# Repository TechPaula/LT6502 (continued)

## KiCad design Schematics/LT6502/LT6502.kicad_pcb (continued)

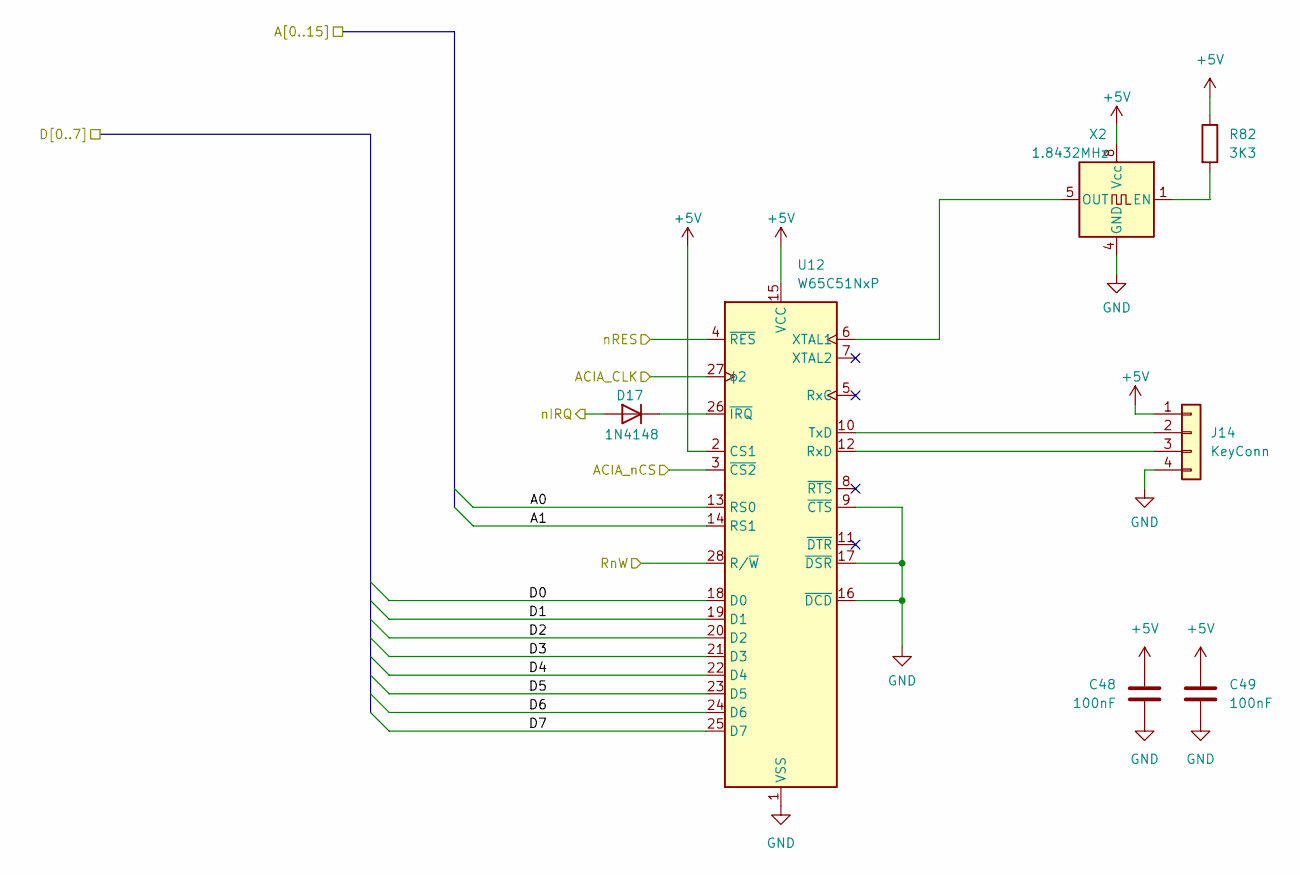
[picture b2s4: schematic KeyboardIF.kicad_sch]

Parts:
C48, C49: 100nF; C_0603_1608Metric; LCSC C113803
D17: 1N4148; D_DO-35_SOD27_P7.62mm_Horizontal; LCSC DNF
J14: KeyConn; PinHeader_1x04_P2.54mm_Horizontal; LCSC DNF
R82: 3K3; R_0402_1005Metric; LCSC C25890
U12: W65C51NxP; DIP-28_W15.24mm; LCSC DNF
X2: 1.8432MHz; Oscillator_DIP-8; Mouser Part Number 774-MXO45HST-3C-1.8; LCSC DNF

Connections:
+5V: C48.1, C49.1, J14.1, R82.1, U12.2 (CS1), U12.15 (VCC), X2.8 (Vcc); also elsewhere on the board
/A0: U12.13 (RS0); also elsewhere on the board
/A1: U12.14 (RS1); also elsewhere on the board
/D0: U12.18 (D0); also elsewhere on the board
/D1: U12.19 (D1); also elsewhere on the board
/D2: U12.20 (D2); also elsewhere on the board
/D3: U12.21 (D3); also elsewhere on the board
/D4: U12.22 (D4); also elsewhere on the board
/D5: U12.23 (D5); also elsewhere on the board
/D6: U12.24 (D6); also elsewhere on the board
/D7: U12.25 (D7); also elsewhere on the board
ACIA_nCS: U12.3 (~CS2); also elsewhere on the board
CLK: U12.27 (ϕ2); also elsewhere on the board
GND: C48.2, C49.2, J14.4, U12.1 (VSS), U12.9 (~CTS), U12.16 (~DCD), U12.17 (~DSR), X2.4 (GND); also elsewhere on the board
unnamed: D17.1 (K), U12.26 (~IRQ)
unnamed: J14.2, U12.10 (TxD)
unnamed: J14.3, U12.12 (RxD)
unnamed: U12.6 (XTAL1), X2.5 (OUT)
unnamed: R82.2, X2.1 (EN)
RnW: U12.28 (R/~W); also elsewhere on the board
nIRQ: D17.2 (A); also elsewhere on the board
nRES: U12.4 (~RES); also elsewhere on the board

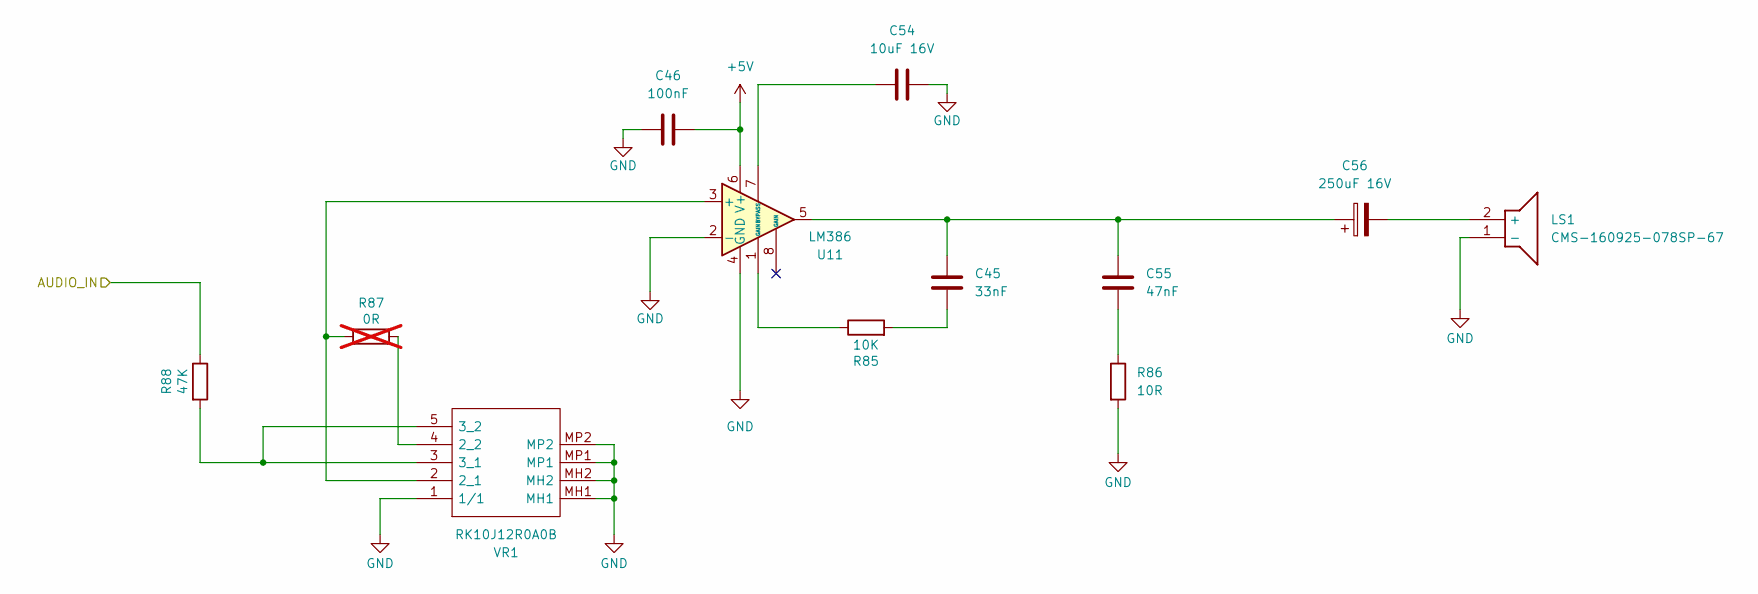
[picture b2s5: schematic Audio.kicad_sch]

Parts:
C45: 33nF; C_0603_1608Metric; LCSC C21117
C46: 100nF; C_0603_1608Metric; LCSC C113803
C54: 10uF 16V; C_0805_2012Metric; LCSC C15850
C55: 47nF; C_0603_1608Metric; LCSC C1622
C56: 250uF 16V; CP_Elec_10x12.5; Mouser Part Number 667-EEV-FK1V681Q
LS1: CMS-160925-078SP-67; CMS160925078SP67; Mouser Part Number 490-CMS160925078SP67
R85: 10K; R_0402_1005Metric; LCSC C25744
R86: 10R; R_0805_2012Metric; LCSC C844598
R87: 0R; R_0402_1005Metric; LCSC DNF; not fitted
R88: 47K; R_0402_1005Metric; LCSC DNF
U11: LM386; DIP-8_W7.62mm; Mouser Part Number 926-LM386N-3/NOPB
VR1: RK10J12R0A0B; Mouser Part Number 688-RK10J12R0A0B

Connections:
+5V: C46.2, U11.6 (V+); also elsewhere on the board
AUDIO: R88.1; also elsewhere on the board
GND: C46.1, C54.1, LS1.1 (-), R86.2, U11.2 (-), U11.4 (GND), VR1.1 (1/1), VR1.MH1, VR1.MH2, VR1.MP1, VR1.MP2; also elsewhere on the board
unnamed: C45.1, C55.1, C56.1, U11.5
unnamed: C45.2, R85.2
unnamed: C55.2, R86.1
unnamed: C56.2, LS1.2 (+)
unnamed: R85.1, U11.1 (GAIN)
unnamed: R87.2, U11.3 (+), VR1.2 (2_1)
unnamed: C54.2, U11.7 (BYPASS)
unnamed: R87.1, VR1.4 (2_2)
unnamed: R88.2, VR1.3 (3_1), VR1.5 (3_2)

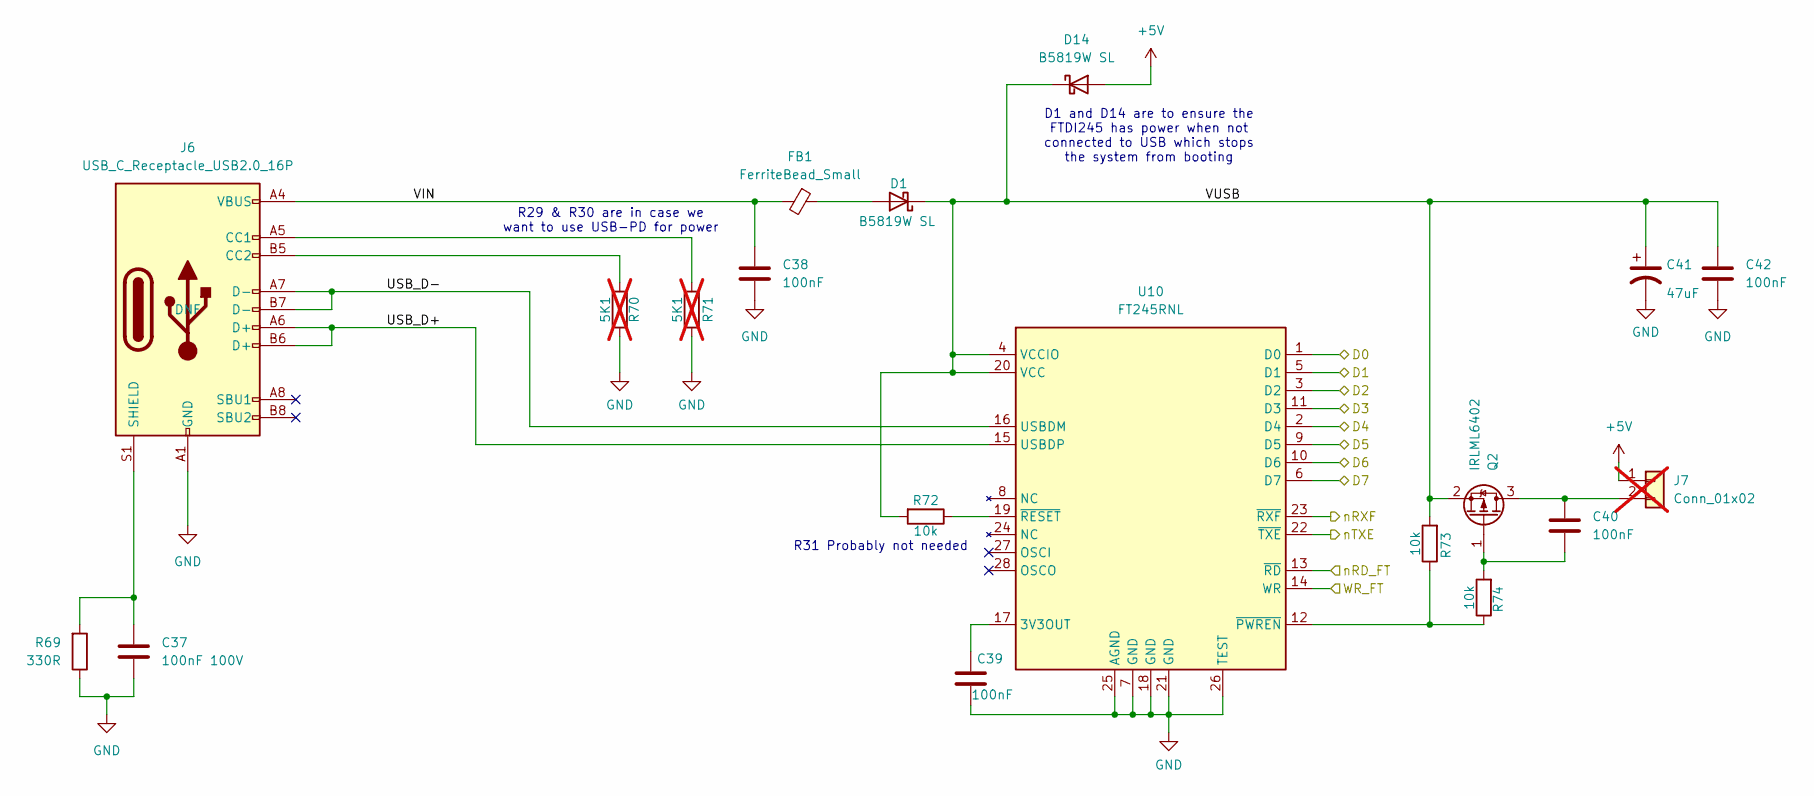
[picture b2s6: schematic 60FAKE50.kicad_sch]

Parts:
C37: 100nF 100V; C_0603_1608Metric; LCSC C113803
C38, C42: 100nF; C_0805_2012Metric; LCSC C49678
C39, C40: 100nF; C_0603_1608Metric; LCSC C113803
C41: 47uF; C_1206_3216Metric; LCSC C22367835
D1, D14: B5819W SL; D_SOD-123; LCSC C8598
FB1: FerriteBead_Small; L_0805_2012Metric_Pad1.05x1.20mm_HandSolder; LCSC DNF
J6: USB_C_Receptacle_USB2.0_16P; USB_C_Receptacle_HCTL_HC-TYPE-C-16P-01A; LCSC DNF
J7: Conn_01x02; PinHeader_1x02_P2.54mm_Horizontal; LCSC DNF; not fitted
Q2: IRLML6402; SOT-23; Mouser Part Number 942-IRLML6402TRPBF; LCSC C2593
R69: 330R; R_0402_1005Metric; LCSC C25104
R70, R71: 5K1; R_0402_1005Metric; LCSC DNF; not fitted
R72, R73, R74: 10k; R_0402_1005Metric; LCSC C25744
U10: FT245RNL; SSOP-28_5.3x10.2mm_P0.65mm; Mouser Part Number 895-FT245RNL-REEL; LCSC DNF

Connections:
+5V: D14.2 (A), J7.1; also elsewhere on the board
/60FAKE50/USB_D+: J6.A6 (D+), J6.B6 (D+), U10.15 (USBDP)
/60FAKE50/USB_D-: J6.A7 (D-), J6.B7 (D-), U10.16 (USBDM)
/60FAKE50/VIN: C38.1, FB1.2, J6.A4 (VBUS), J6.A9 (VBUS), J6.B4 (VBUS), J6.B9 (VBUS)
/60FAKE50/VUSB: C41.1, C42.1, D1.1 (K), D14.1 (K), Q2.2 (S), R72.2, R73.2, U10.4 (VCCIO), U10.20 (VCC)
/D0: U10.1 (D0); also elsewhere on the board
/D1: U10.5 (D1); also elsewhere on the board
/D2: U10.3 (D2); also elsewhere on the board
/D3: U10.11 (D3); also elsewhere on the board
/D4: U10.2 (D4); also elsewhere on the board
/D5: U10.9 (D5); also elsewhere on the board
/D6: U10.10 (D6); also elsewhere on the board
/D7: U10.6 (D7); also elsewhere on the board
GND: C37.2, C38.2, C39.2, C41.2, C42.2, J6.A1 (GND), J6.A12 (GND), J6.B1 (GND), J6.B12 (GND), R69.1, R70.1, R71.1, U10.7 (GND), U10.18 (GND), U10.21 (GND), U10.25 (AGND), U10.26 (TEST); also elsewhere on the board
unnamed: D1.2 (A), FB1.1
unnamed: J6.A5 (CC1), R71.2
unnamed: J6.B5 (CC2), R70.2
unnamed: C37.1, J6.S1 (SHIELD), R69.2
unnamed: C40.1, J7.2, Q2.3 (D)
unnamed: C40.2, Q2.1 (G), R74.2
unnamed: C39.1, U10.17 (3V3OUT)
unnamed: R73.1, R74.1, U10.12 (~PWREN)
unnamed: R72.1, U10.19 (~RESET)
WR_FT: U10.14 (WR); also elsewhere on the board
nRD_FT: U10.13 (~RD); also elsewhere on the board
nRXF: U10.23 (~RXF); also elsewhere on the board
nTXE: U10.22 (~TXE); also elsewhere on the board

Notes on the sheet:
D1 and D14 are to ensure the FTDI245 has power when not connected to USB which stops the system from booting
R31 Probably not needed
R29 & R30 are in case we want to use USB-PD for power

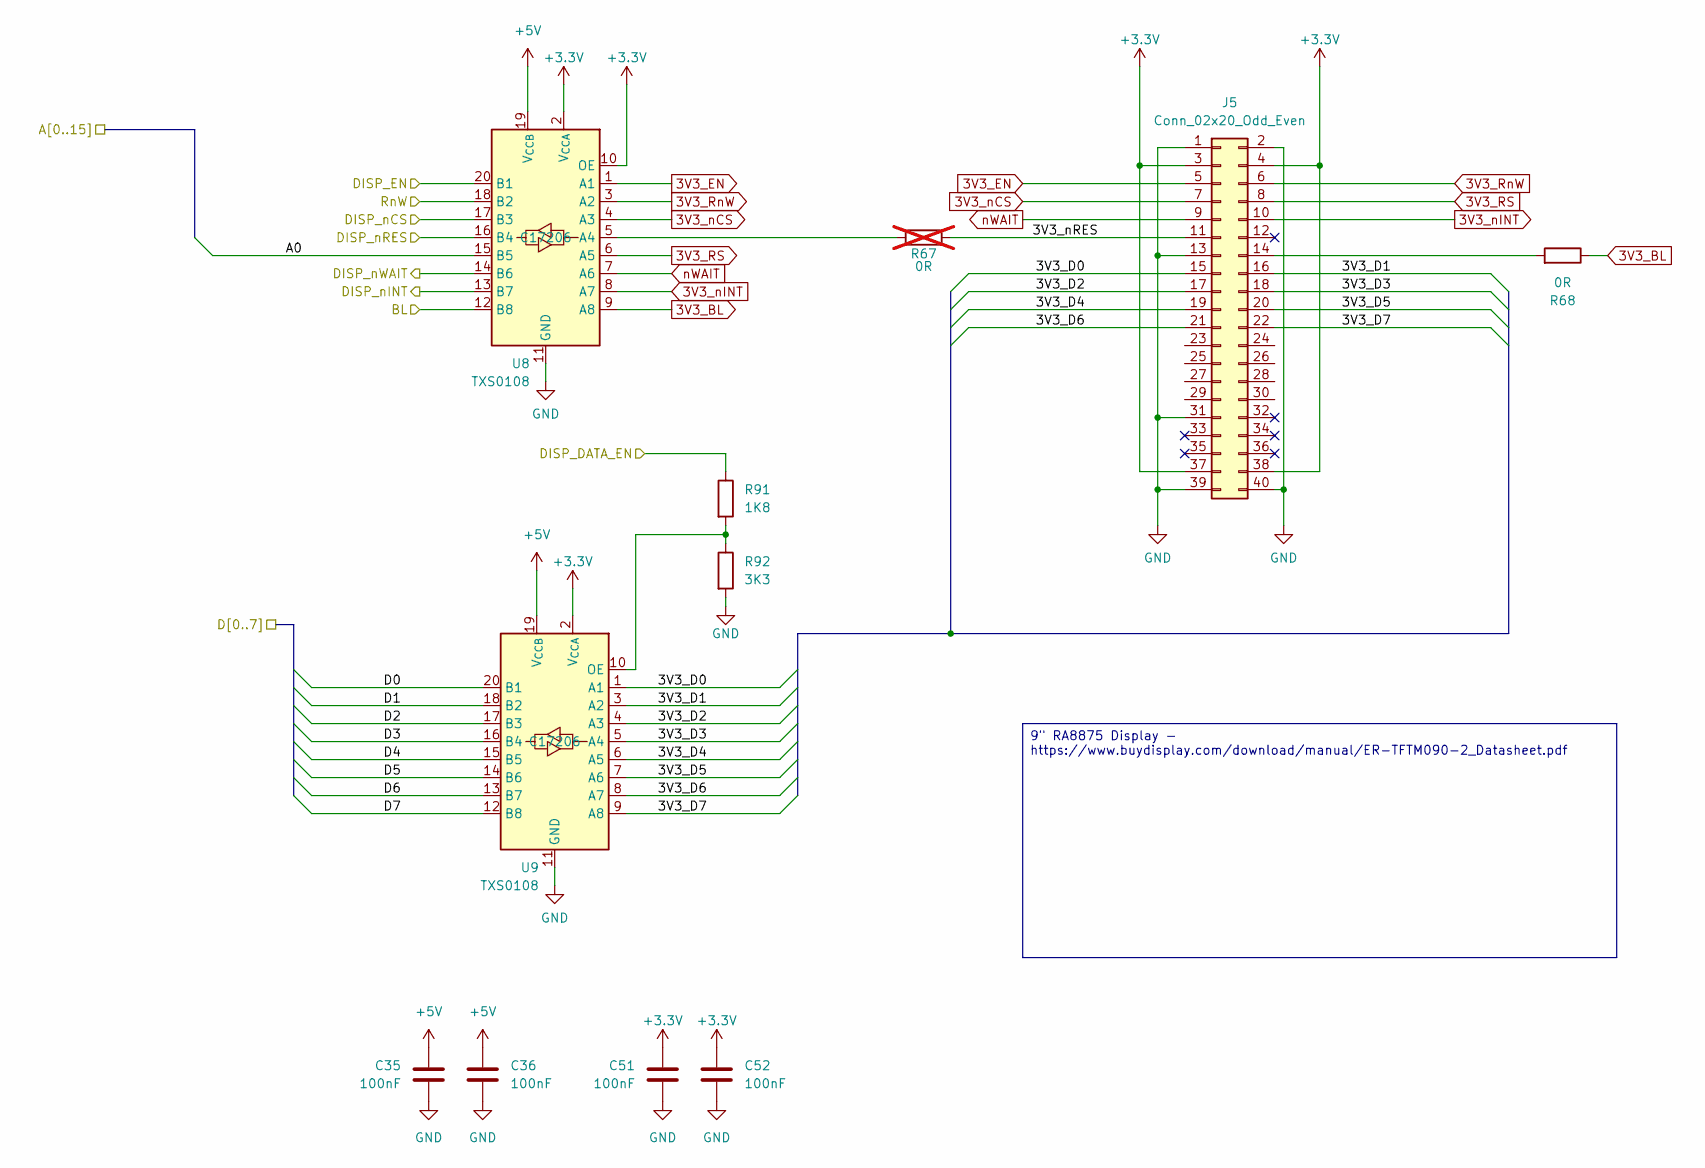
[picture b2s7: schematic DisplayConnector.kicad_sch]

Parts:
C35, C36, C51, C52: 100nF; C_0603_1608Metric; LCSC C113803
J5: Conn_02x20_Odd_Even; PinHeader_2x20_P2.54mm_Vertical; LCSC DNF
R67: 0R; R_0402_1005Metric; LCSC DNF; not fitted
R68: 0R; R_0402_1005Metric; LCSC DNF
R91: 1K8; R_0603_1608Metric; LCSC C25890
R92: 3K3; R_0603_1608Metric; LCSC C25890
U8, U9: TXS0108; TSSOP-20_4.4x6.5mm_P0.65mm; Mouser Part Number 595-TXB0108PWR; LCSC C17206

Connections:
3V3_BL: R68.1, U8.9 (A8)
3V3_EN: J5.5, U8.1 (A1)
3V3_RS: J5.8, U8.6 (A5)
3V3_RnW: J5.6, U8.3 (A2)
3V3_nCS: J5.7, U8.4 (A3)
3V3_nINT: J5.10, U8.8 (A7)
+3.3V: C51.1, C52.1, J5.3, J5.4, J5.37, J5.38, U8.2 (V_{CCA}), U8.10 (OE), U9.2 (V_{CCA}); also elsewhere on the board
+5V: C35.1, C36.1, U8.19 (V_{CCB}), U9.19 (V_{CCB}); also elsewhere on the board
/A0: U8.15 (B5); also elsewhere on the board
/D0: U9.20 (B1); also elsewhere on the board
/D1: U9.18 (B2); also elsewhere on the board
/D2: U9.17 (B3); also elsewhere on the board
/D3: U9.16 (B4); also elsewhere on the board
/D4: U9.15 (B5); also elsewhere on the board
/D5: U9.14 (B6); also elsewhere on the board
/D6: U9.13 (B7); also elsewhere on the board
/D7: U9.12 (B8); also elsewhere on the board
/Display Connector/3V3_D0: J5.15, U9.1 (A1)
/Display Connector/3V3_D1: J5.16, U9.3 (A2)
/Display Connector/3V3_D2: J5.17, U9.4 (A3)
/Display Connector/3V3_D3: J5.18, U9.5 (A4)
/Display Connector/3V3_D4: J5.19, U9.6 (A5)
/Display Connector/3V3_D5: J5.20, U9.7 (A6)
/Display Connector/3V3_D6: J5.21, U9.8 (A7)
/Display Connector/3V3_D7: J5.22, U9.9 (A8)
/Display Connector/3V3_nRES: J5.11, R67.2
/Display Connector/BL: U8.12 (B8); also elsewhere on the board
/Display Connector/DISP_DATA_EN: R91.1; also elsewhere on the board
/Display Connector/DISP_EN: U8.20 (B1); also elsewhere on the board
/Display Connector/DISP_nCS: U8.17 (B3); also elsewhere on the board
/Display Connector/DISP_nINT: U8.13 (B7); also elsewhere on the board
/Display Connector/DISP_nRES: U8.16 (B4); also elsewhere on the board
/Display Connector/DISP_nWAIT: U8.14 (B6); also elsewhere on the board
GND: C35.2, C36.2, C51.2, C52.2, J5.1, J5.2, J5.13, J5.31, J5.39, J5.40, R92.2, U8.11 (GND), U9.11 (GND); also elsewhere on the board
unnamed: J5.14, R68.2
unnamed: R67.1, U8.5 (A4)
unnamed: R91.2, R92.1, U9.10 (OE)
RnW: U8.18 (B2); also elsewhere on the board
nWAIT: J5.9, U8.7 (A6)

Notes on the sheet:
9" RA8875 Display - https://www.buydisplay.com/download/manual/ER-TFTM090-2_Datasheet.pdf

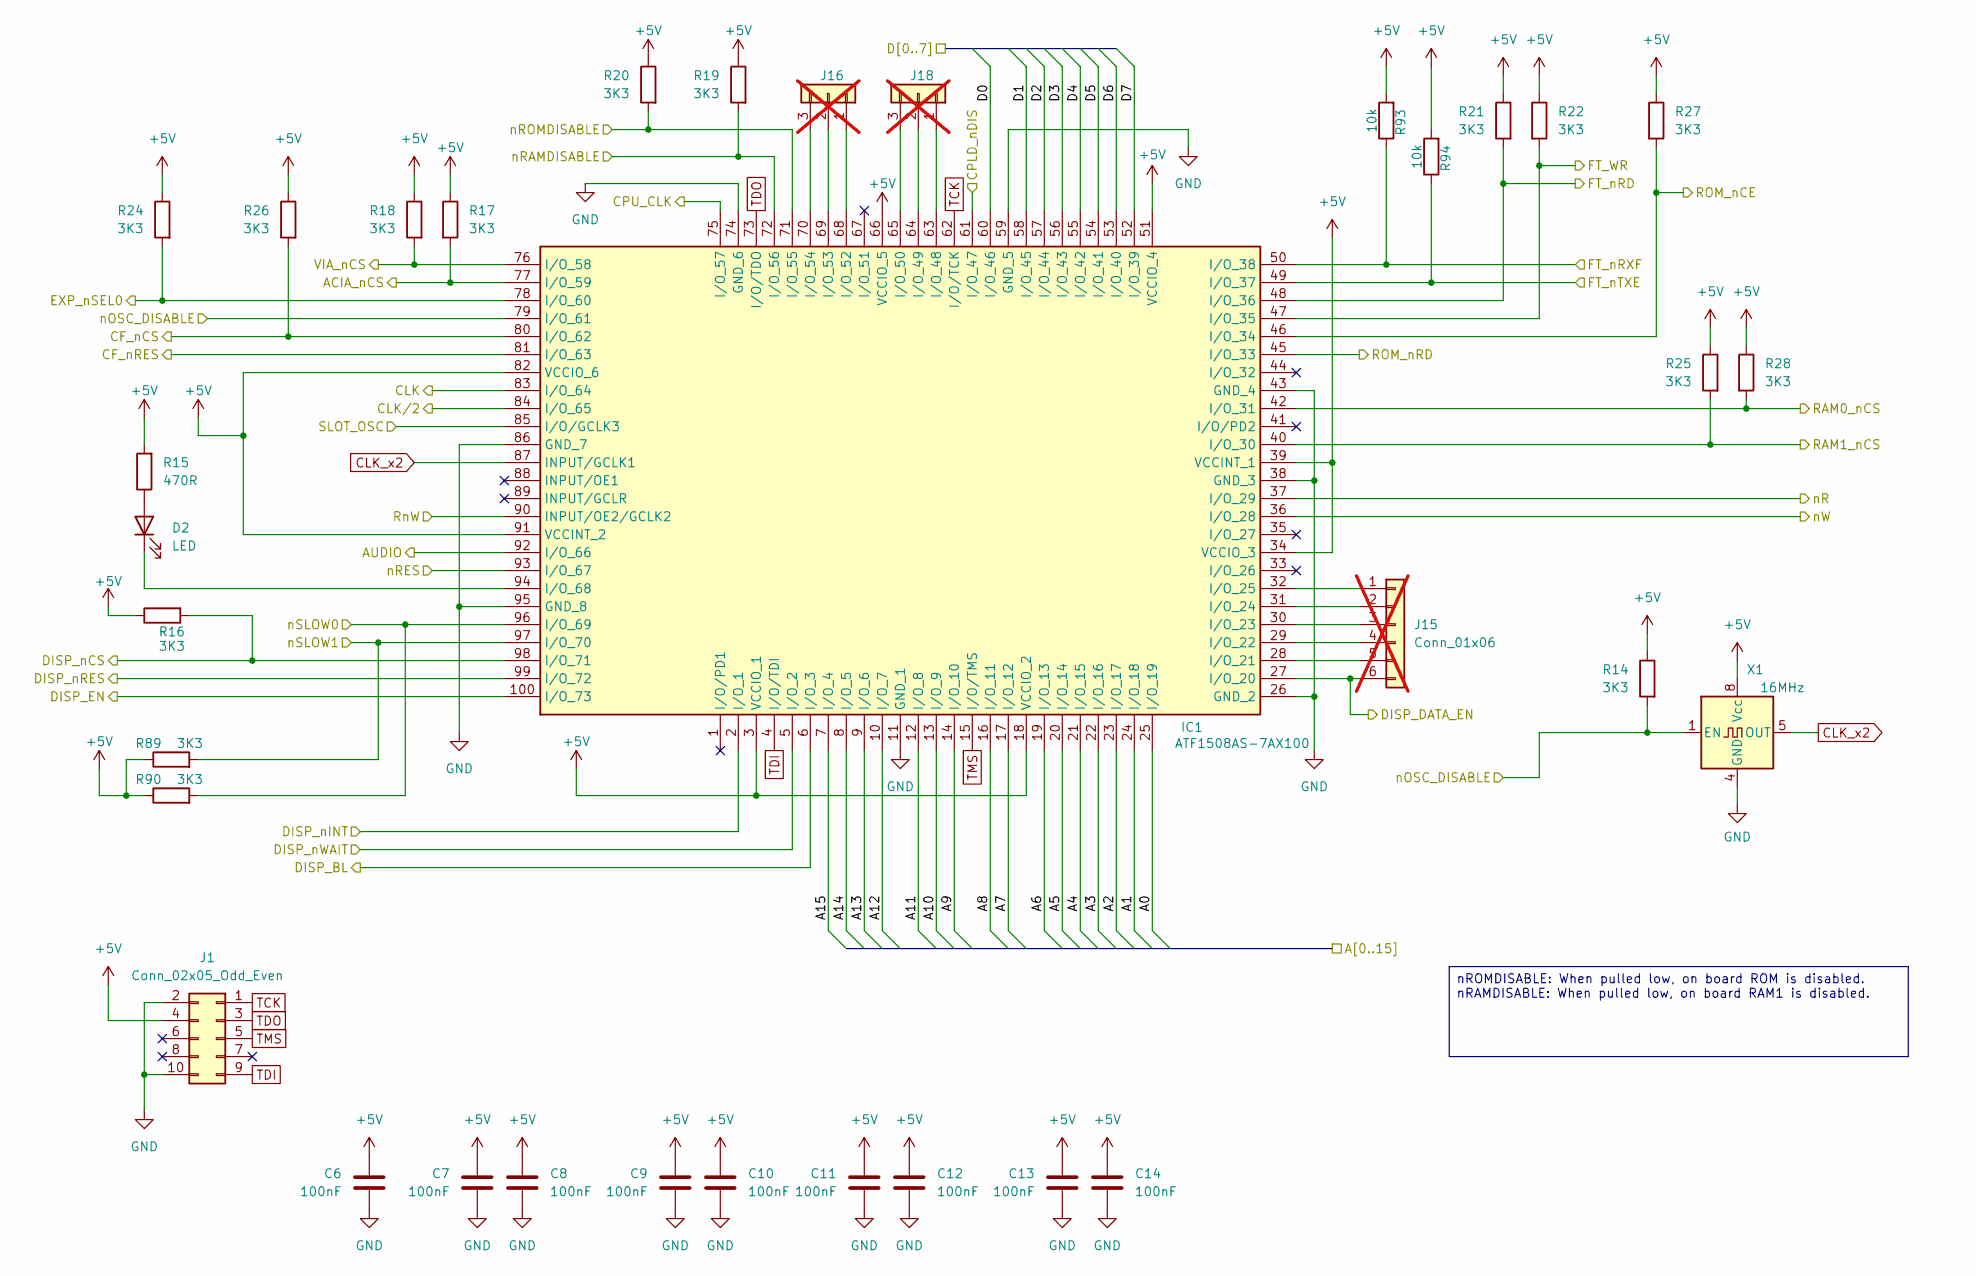
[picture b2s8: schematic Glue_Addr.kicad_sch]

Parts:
C6, C7, C8, C9, C11, C12, C13, C14: 100nF; C_0603_1608Metric; LCSC C113803
C10: 100nF; C_0402_1005Metric; LCSC C1581
D2: LED; LED_0603_1608Metric; LCSC DNF
IC1: ATF1508AS-7AX100; QFP50P1600X1600X120-100N; Mouser Part Number 556-AF1508AS7AX100
J1: Conn_02x05_Odd_Even; PinHeader_2x05_P2.54mm_Horizontal; LCSC DNF
J15: Conn_01x06; PinHeader_1x06_P1.00mm_Vertical_SMD_Pin1Left; LCSC DNF; not fitted
J16, J18: Conn_01x03; PinHeader_1x03_P1.00mm_Vertical_SMD_Pin1Left; LCSC DNF; not fitted
R14, R16, R17, R18, R19, R20, R21, R22, R24, R25, R26, R27, R28, R89, R90: 3K3; R_0402_1005Metric; LCSC C25890
R15: 470R; R_0402_1005Metric; LCSC C25117
R93, R94: 10k; R_0402_1005Metric; LCSC C25744
X1: 16MHz; Oscillator_DIP-8; Mouser Part Number 520-2100AX-283.2; LCSC DNF

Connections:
+5V: C6.1, C7.1, C8.1, C9.1, C10.1, C11.1, C12.1, C13.1, C14.1, IC1.3 (VCCIO_1), IC1.18 (VCCIO_2), IC1.34 (VCCIO_3), IC1.39 (VCCINT_1), IC1.51 (VCCIO_4), IC1.66 (VCCIO_5), IC1.82 (VCCIO_6), IC1.91 (VCCINT_2), J1.4, R14.1, R15.2, R16.1, R17.1, R18.1, R19.1, R20.1, R21.1, R22.1, R24.1, R25.1, R26.1, R27.1, R28.1, R89.1, R90.1, R93.2, R94.2, X1.8 (Vcc); also elsewhere on the board
/A0: IC1.25 (I/O_19); also elsewhere on the board
/A1: IC1.24 (I/O_18); also elsewhere on the board
/A2: IC1.23 (I/O_17); also elsewhere on the board
/A3: IC1.22 (I/O_16); also elsewhere on the board
/A4: IC1.21 (I/O_15); also elsewhere on the board
/A5: IC1.20 (I/O_14); also elsewhere on the board
/A6: IC1.19 (I/O_13); also elsewhere on the board
/A7: IC1.17 (I/O_12); also elsewhere on the board
/A8: IC1.16 (I/O_11); also elsewhere on the board
/A9: IC1.14 (I/O_10); also elsewhere on the board
/A10: IC1.13 (I/O_9); also elsewhere on the board
/A11: IC1.12 (I/O_8); also elsewhere on the board
/A12: IC1.10 (I/O_7); also elsewhere on the board
/A13: IC1.9 (I/O_6); also elsewhere on the board
/A14: IC1.8 (I/O_5); also elsewhere on the board
/A15: IC1.7 (I/O_4); also elsewhere on the board
/D0: IC1.60 (I/O_46); also elsewhere on the board
/D1: IC1.58 (I/O_45); also elsewhere on the board
/D2: IC1.57 (I/O_44); also elsewhere on the board
/D3: IC1.56 (I/O_43); also elsewhere on the board
/D4: IC1.55 (I/O_42); also elsewhere on the board
/D5: IC1.54 (I/O_41); also elsewhere on the board
/D6: IC1.53 (I/O_40); also elsewhere on the board
/D7: IC1.52 (I/O_39); also elsewhere on the board
/Display Connector/BL: IC1.6 (I/O_3); also elsewhere on the board
/Display Connector/DISP_DATA_EN: IC1.27 (I/O_20), J15.6; also elsewhere on the board
/Display Connector/DISP_EN: IC1.100 (I/O_73); also elsewhere on the board
/Display Connector/DISP_nCS: IC1.98 (I/O_71), R16.2; also elsewhere on the board
/Display Connector/DISP_nINT: IC1.2 (I/O_1); also elsewhere on the board
/Display Connector/DISP_nRES: IC1.99 (I/O_72); also elsewhere on the board
/Display Connector/DISP_nWAIT: IC1.5 (I/O_2); also elsewhere on the board
/ExpansionSlot0/CPLD_nDIS: IC1.61 (I/O_47); also elsewhere on the board
ACIA_nCS: IC1.77 (I/O_59), R17.2; also elsewhere on the board
AUDIO: IC1.92 (I/O_66); also elsewhere on the board
CFnRES: IC1.80 (I/O_62), R26.2; also elsewhere on the board
CLK: IC1.83 (I/O_64); also elsewhere on the board
CLK_x2: IC1.87 (INPUT/GCLK1), X1.5 (OUT)
CLK/2: IC1.84 (I/O_65); also elsewhere on the board
CPU_CLK: IC1.75 (I/O_57); also elsewhere on the board
EXP_nSEL0: IC1.78 (I/O_60), R24.2; also elsewhere on the board
GND: C6.2, C7.2, C8.2, C9.2, C10.2, C11.2, C12.2, C13.2, C14.2, IC1.11 (GND_1), IC1.26 (GND_2), IC1.38 (GND_3), IC1.43 (GND_4), IC1.59 (GND_5), IC1.74 (GND_6), IC1.86 (GND_7), IC1.95 (GND_8), J1.2, J1.10, X1.4 (GND); also elsewhere on the board
unnamed: D2.2 (A), R15.1
unnamed: D2.1 (K), IC1.94 (I/O_68)
unnamed: IC1.28 (I/O_21), J15.5
unnamed: IC1.29 (I/O_22), J15.4
unnamed: IC1.30 (I/O_23), J15.3
unnamed: IC1.31 (I/O_24), J15.2
unnamed: IC1.32 (I/O_25), J15.1
unnamed: IC1.63 (I/O_48), J18.1
unnamed: IC1.64 (I/O_49), J18.2
unnamed: IC1.65 (I/O_50), J18.3
unnamed: IC1.68 (I/O_52), J16.1
unnamed: IC1.69 (I/O_53), J16.2
unnamed: IC1.70 (I/O_54), J16.3
ROM_nCE: IC1.46 (I/O_34), R27.2; also elsewhere on the board
ROM_nR: IC1.45 (I/O_33); also elsewhere on the board
RnW: IC1.90 (INPUT/OE2/GCLK2); also elsewhere on the board
SLOT_OSC: IC1.85 (I/O/GCLK3); also elsewhere on the board
TCK: IC1.62 (I/O/TCK), J1.1
TDI: IC1.4 (I/O/TDI), J1.9
TDO: IC1.73 (I/O/TDO), J1.3
TMS: IC1.15 (I/O/TMS), J1.5
VIA_nCS: IC1.76 (I/O_58), R18.2; also elsewhere on the board
WR_FT: IC1.47 (I/O_35), R22.2; also elsewhere on the board
nCF_CS0: IC1.81 (I/O_63); also elsewhere on the board
nOSC_DISABLE: IC1.79 (I/O_61), R14.2, X1.1 (EN); also elsewhere on the board
nR: IC1.37 (I/O_29); also elsewhere on the board
nRAM0_CS: IC1.42 (I/O_31), R28.2; also elsewhere on the board
nRAM1_CS: IC1.40 (I/O_30), R25.2; also elsewhere on the board
nRAMDISABLE: IC1.72 (I/O_56), R19.2; also elsewhere on the board
nRD_FT: IC1.48 (I/O_36), R21.2; also elsewhere on the board
nRES: IC1.93 (I/O_67); also elsewhere on the board
nROMDISABLE: IC1.71 (I/O_55), R20.2; also elsewhere on the board
nRXF: IC1.49 (I/O_37), R94.1; also elsewhere on the board
nSLOW0: IC1.96 (I/O_69), R90.2; also elsewhere on the board
nSLOW1: IC1.97 (I/O_70), R89.2; also elsewhere on the board
nTXE: IC1.50 (I/O_38), R93.1; also elsewhere on the board
nW: IC1.36 (I/O_28); also elsewhere on the board

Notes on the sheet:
nROMDISABLE: When pulled low, on board ROM is disabled. nRAMDISABLE: When pulled low, on board RAM1 is disabled.

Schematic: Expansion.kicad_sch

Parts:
C43: 100nF; C_0603_1608Metric; LCSC C113803
C44: 22uF 25V; C_0805_2012Metric; LCSC C45783
D12, D13, D19, D21: 1N4148; D_DO-35_SOD27_P7.62mm_Horizontal; LCSC DNF
J9: DIN41612_02x32_AC; DIN41612_R_2x32_Female_Horizontal_THT; Mouser Part Number 649-864648813H55V1LF
R23: 3K3; R_0402_1005Metric; LCSC C25890

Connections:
+5V: C43.1, C44.1, J9.a2, J9.a31, J9.c2, J9.c31, R23.1; also elsewhere on the board
/A0: J9.c18; also elsewhere on the board
/A1: J9.a18; also elsewhere on the board
/A2: J9.c17; also elsewhere on the board
/A3: J9.a17; also elsewhere on the board
/A4: J9.c16; also elsewhere on the board
/A5: J9.a16; also elsewhere on the board
/A6: J9.c15; also elsewhere on the board
/A7: J9.a15; also elsewhere on the board
/A8: J9.c14; also elsewhere on the board
/A9: J9.a14; also elsewhere on the board
/A10: J9.c13; also elsewhere on the board
/A11: J9.a13; also elsewhere on the board
/A12: J9.c12; also elsewhere on the board
/A13: J9.a12; also elsewhere on the board
/A14: J9.c11; also elsewhere on the board
/A15: J9.a11; also elsewhere on the board
/D0: J9.c20; also elsewhere on the board
/D1: J9.a20; also elsewhere on the board
/D2: J9.c21; also elsewhere on the board
/D3: J9.a21; also elsewhere on the board
/D4: J9.c22; also elsewhere on the board
/D5: J9.a22; also elsewhere on the board
/D6: J9.c23; also elsewhere on the board
/D7: J9.a23; also elsewhere on the board
/ExpansionSlot0/CPLD_nDIS: J9.a28, R23.2; also elsewhere on the board
BE: J9.a25; also elsewhere on the board
CLK: J9.c8; also elsewhere on the board
CLK/2: J9.c9; also elsewhere on the board
CPU_CLK: J9.c7; also elsewhere on the board
EXP_nSEL0: J9.c30; also elsewhere on the board
GND: C43.2, C44.2, J9.a1, J9.a6, J9.a10, J9.a19, J9.a32, J9.c1, J9.c6, J9.c10, J9.c19, J9.c32; also elsewhere on the board
unnamed: D12.1 (K), J9.a29
unnamed: D13.1 (K), J9.a30
unnamed: D19.1 (K), J9.c28
unnamed: D21.1 (K), J9.c29
PHI1O: J9.a7; also elsewhere on the board
PHI2O: J9.a8; also elsewhere on the board
RDY: J9.a24; also elsewhere on the board
RnW: J9.c4; also elsewhere on the board
SLOT_OSC: J9.a9; also elsewhere on the board
SYNQ: J9.c25; also elsewhere on the board
nIRQ: J9.a27; also elsewhere on the board
nML: J9.c26; also elsewhere on the board
nNMI: J9.c27; also elsewhere on the board
nOSC_DISABLE: J9.a5; also elsewhere on the board
nRAMDISABLE: D12.2 (A); also elsewhere on the board
nRES: J9.c5; also elsewhere on the board
nROMDISABLE: D13.2 (A); also elsewhere on the board
nSLOW0: D19.2 (A); also elsewhere on the board
nSLOW1: D21.2 (A); also elsewhere on the board
nSO: J9.a26; also elsewhere on the board
nVP: J9.c24; also elsewhere on the board

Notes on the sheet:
I should have routed CLK/2 to the VIA/ACIA instead of the 16MHz Clock So I've swapped them in the CPLD.
As I'm unsure what I will do with these ports in the future I've added every CPU pin and a bunch of others that might be useful. nROMDISABLE: When pulled low, on board ROM is disabled. nRAMDISABLE: When pulled low, on board RAM1 is disabled. CPU_CLK could be stretched CLK is unstretched main clock 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

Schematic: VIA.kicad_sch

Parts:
C47: 100nF; C_0603_1608Metric; LCSC C113803
D16: 1N4148; D_DO-35_SOD27_P7.62mm_Horizontal; LCSC DNF
IC3: W65C22S6TQG-14; QFP80P1320X1320X270-44N; Mouser Part Number 955-W65C22S6TQG-14
J11: Conn_02x04_Odd_Even; PinSocket_2x04_P2.54mm_Horizontal; LCSC DNF
J12, J13: Conn_02x06_Odd_Even; PinSocket_2x06_P2.54mm_Horizontal; LCSC DNF

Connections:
+5V: C47.1, IC3.15 (VDD), IC3.20 (CS1), J11.1, J11.2, J12.1, J12.2, J13.1, J13.2; also elsewhere on the board
/A0: IC3.36 (RS0); also elsewhere on the board
/A1: IC3.35 (RS1); also elsewhere on the board
/A2: IC3.34 (RS2); also elsewhere on the board
/A3: IC3.33 (RS3); also elsewhere on the board
/D0: IC3.30 (D0); also elsewhere on the board
/D1: IC3.29 (D1); also elsewhere on the board
/D2: IC3.28 (D2); also elsewhere on the board
/D3: IC3.26 (D3); also elsewhere on the board
/D4: IC3.25 (D4); also elsewhere on the board
/D5: IC3.24 (D5); also elsewhere on the board
/D6: IC3.23 (D6); also elsewhere on the board
/D7: IC3.22 (D7); also elsewhere on the board
/VIA/VA_CA1: IC3.37 (CA2), J11.7
/VIA/VA_CA2: IC3.38 (CA1), J11.5
/VIA/VA_CB1: IC3.13 (CB1), J11.8
/VIA/VA_CB2: IC3.14 (CB2), J11.6
/VIA/VA_PA0: IC3.40 (PA0), J13.11
/VIA/VA_PA1: IC3.41 (PA1), J13.9
/VIA/VA_PA2: IC3.42 (PA2), J13.7
/VIA/VA_PA3: IC3.43 (PA3), J13.5
/VIA/VA_PA4: IC3.44 (PA4), J13.12
/VIA/VA_PA5: IC3.1 (PA5), J13.10
/VIA/VA_PA6: IC3.2 (PA6), J13.8
/VIA/VA_PA7: IC3.3 (PA7), J13.6
/VIA/VA_PB0: IC3.4 (PB0), J12.11
/VIA/VA_PB1: IC3.6 (PB1), J12.9
/VIA/VA_PB2: IC3.7 (PB2), J12.7
/VIA/VA_PB3: IC3.8 (PB3), J12.5
/VIA/VA_PB4: IC3.9 (PB4), J12.12
/VIA/VA_PB5: IC3.10 (PB5), J12.10
/VIA/VA_PB6: IC3.11 (PB6), J12.8
/VIA/VA_PB7: IC3.12 (PB7), J12.6
CLK: IC3.21 (PHI2); also elsewhere on the board
GND: C47.2, IC3.39 (VSS), J11.3, J11.4, J12.3, J12.4, J13.3, J13.4; also elsewhere on the board
unnamed: D16.1 (K), IC3.17 (IRQB)
RnW: IC3.18 (IRWB); also elsewhere on the board
VIA_nCS: IC3.19 (CS2B); also elsewhere on the board
nIRQ: D16.2 (A); also elsewhere on the board
nRES: IC3.31 (RESB); also elsewhere on the board

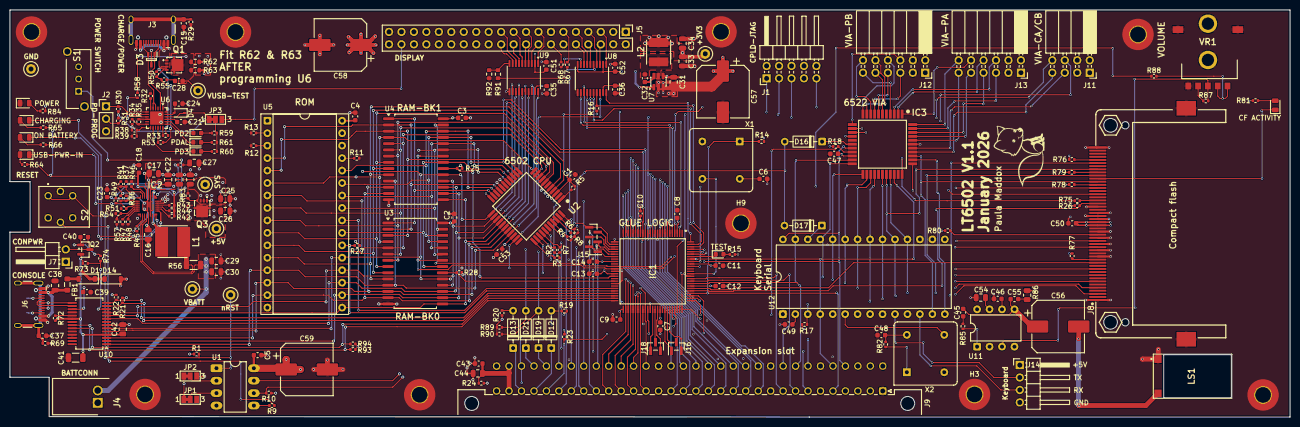
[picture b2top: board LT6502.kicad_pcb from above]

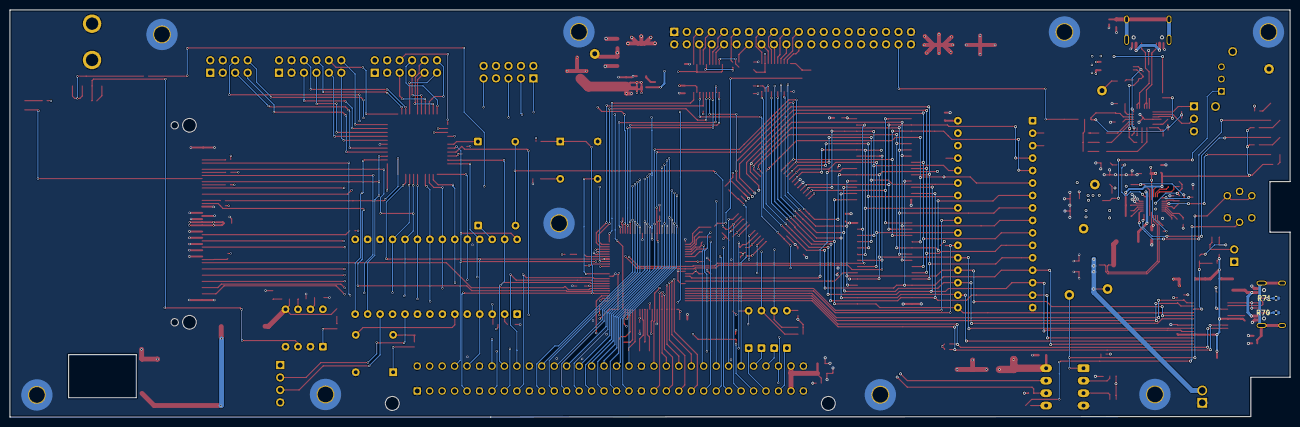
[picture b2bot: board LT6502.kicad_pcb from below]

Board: 4 copper layers, 261.0 x 83.0 mm, 235 parts (2 on the bottom side), 232 nets.
